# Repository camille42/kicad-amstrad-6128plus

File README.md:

# kicad-amstrad-6128plus

My first big project with Kicad.

As i'm not an expert, don't expect everything to be perfect in the first release.

For the first release, i focussed on :
    ** Memory
    ** RGB signal

* For Schematics :
    There is differences between the hardware & schematics & documentation
    ** Some values for resistors are different
    ** the R182 is replaced by a bridge & not present in the documentation
    ** ...

* For PCB :
    I can't find proper elements like keyboard connector, RJ6, centronic, so as it takes
    time to produce, it is not yet correct.

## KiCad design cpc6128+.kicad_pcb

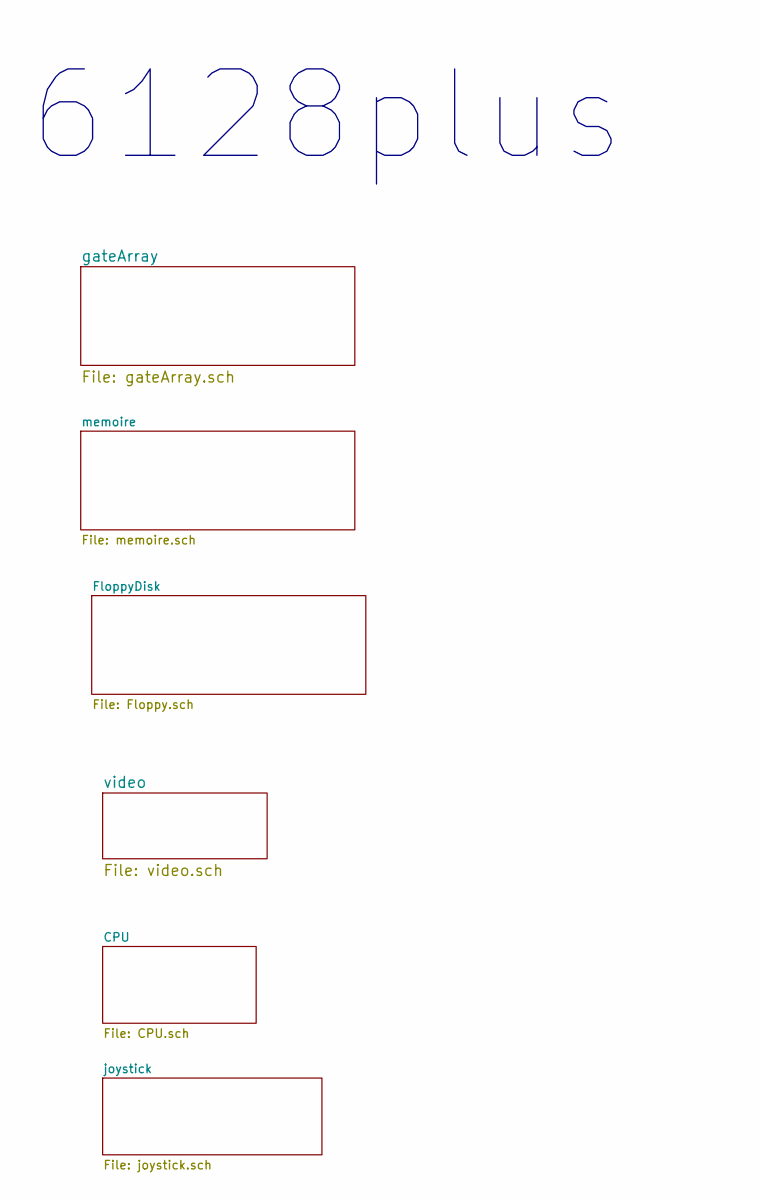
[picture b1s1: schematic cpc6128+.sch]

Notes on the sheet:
6128plus

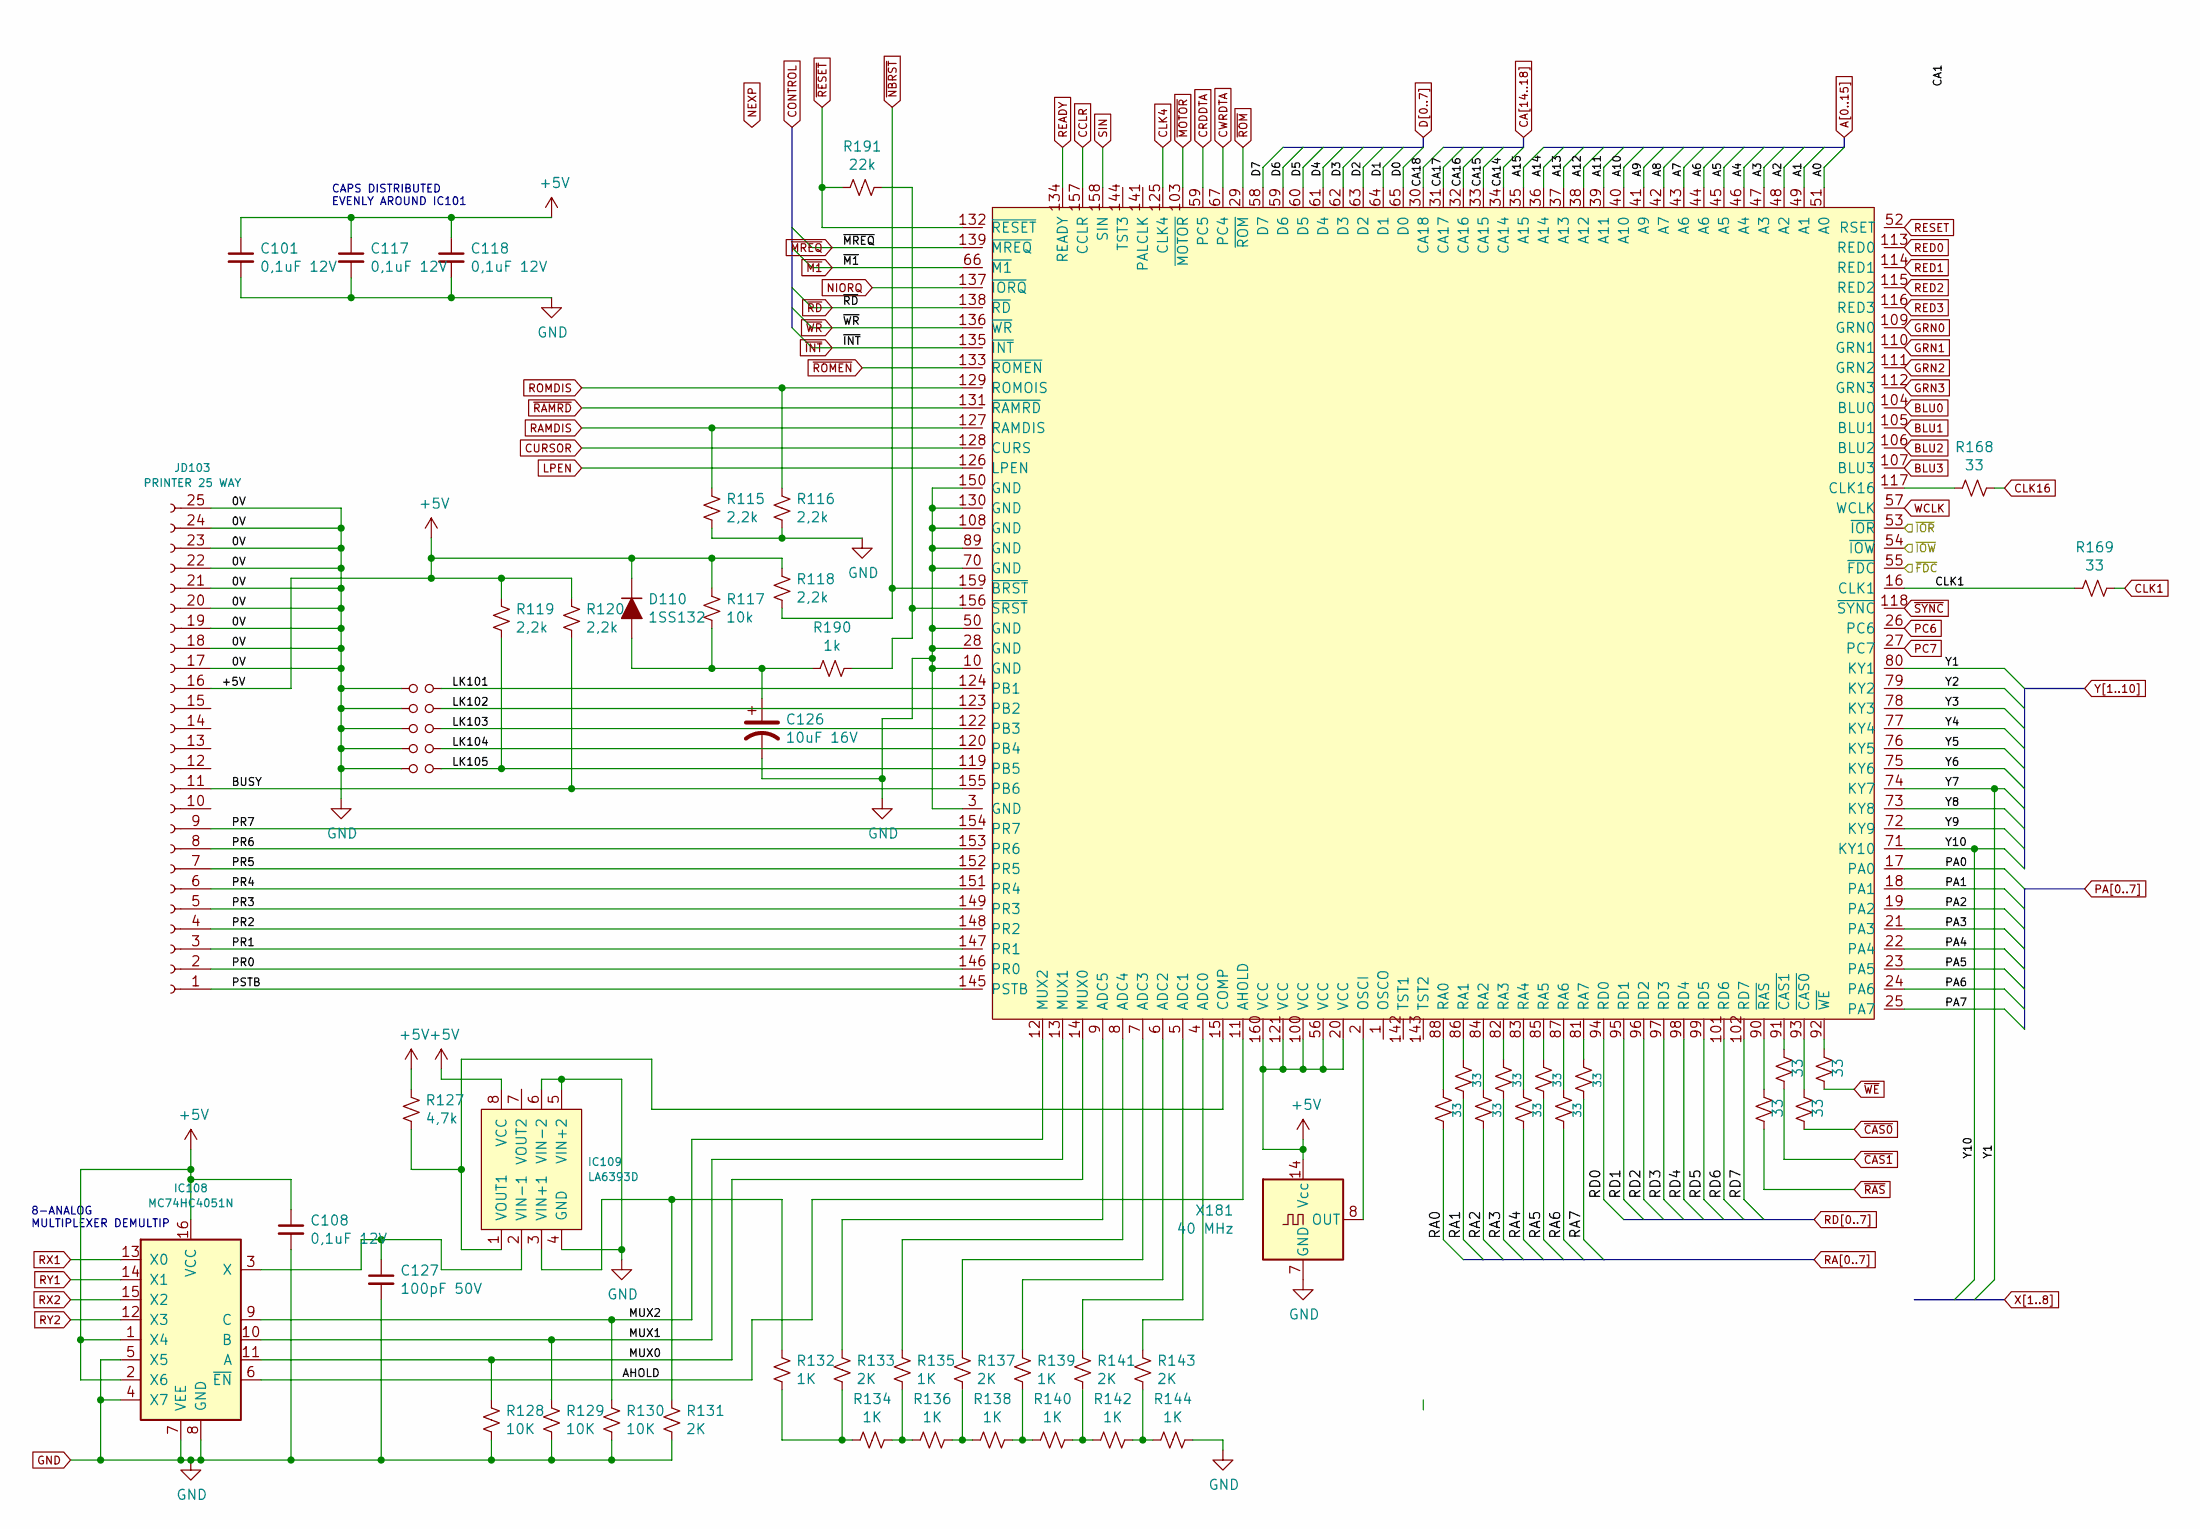
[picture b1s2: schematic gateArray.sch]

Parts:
C101, C108, C117, C118: 0,1uF 12V; C_Disc_D5.0mm_W2.5mm_P5.00mm
C126: 10uF 16V; CP_Radial_D5.0mm_P2.50mm
C127: 100pF 50V; C_Disc_D5.0mm_W2.5mm_P5.00mm
D110: 1SS132; D_A-405_P7.62mm_Horizontal
IC101: AMS40489; QFP-160_28x28_Pitch0.7mm
IC108: MC74HC4051N; DIP-16_W7.62mm
IC109: LA6393D; DIP-8_W7.62mm
JD103: PRINTER 25 WAY; DSUB-25_Male_Horizontal_P2.77x2.84mm_EdgePinOffset4.94mm_Ho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
LK101, LK102, LK103, LK104, LK105: Jumper_NO_Small
R115, R116, R118, R119, R120: 2,2k; R_Axial_DIN0204_L3.6mm_D1.6mm_P5.08mm_Horizontal
R117: 10k; R_Axial_DIN0204_L3.6mm_D1.6mm_P5.08mm_Horizontal
R127: 4,7k; R_Axial_DIN0204_L3.6mm_D1.6mm_P5.08mm_Horizontal
R128, R129, R130: 10K; R_Axial_DIN0204_L3.6mm_D1.6mm_P5.08mm_Horizontal
R131, R133, R137, R141, R143: 2K; R_Axial_DIN0204_L3.6mm_D1.6mm_P5.08mm_Horizontal
R132, R134, R135, R136, R138, R139, R140, R142, R144: 1K; R_Axial_DIN0204_L3.6mm_D1.6mm_P5.08mm_Horizontal
R146, R147, R148, R149, R150, R151, R152, R153, R154, R155, R156, R157, R168, R169: 33; R_Axial_DIN0204_L3.6mm_D1.6mm_P5.08mm_Horizontal
R190: 1k; R_Axial_DIN0204_L3.6mm_D1.6mm_P5.08mm_Horizontal
R191: 22k; R_Axial_DIN0204_L3.6mm_D1.6mm_P5.08mm_Horizontal
X181: 40 MHz; Oscillator_X181_DIP-14

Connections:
/FloppyDisk/~FDC: IC101.55 (~FDC); also elsewhere on the board
/FloppyDisk/~IOR: IC101.53 (~IOR); also elsewhere on the board
/FloppyDisk/~IOW: IC101.54 (~IOW); also elsewhere on the board
/gateArray/AHOLD: IC101.11 (AHOLD), IC108.6 (~EN)
/gateArray/BUSY: IC101.155 (PB6), JD103.11, R120.2; also elsewhere on the board
/gateArray/MUX0: IC101.14 (MUX0), IC108.11 (A), R128.1
/gateArray/MUX1: IC101.13 (MUX1), IC108.10 (B), R129.1
/gateArray/MUX2: IC101.12 (MUX2), IC108.9 (C), R130.1
/gateArray/PR0: IC101.146 (PR0), JD103.2
/gateArray/PR1: IC101.147 (PR1), JD103.3; also elsewhere on the board
/gateArray/PR2: IC101.148 (PR2), JD103.4; also elsewhere on the board
/gateArray/PR3: IC101.149 (PR3), JD103.5; also elsewhere on the board
/gateArray/PR4: IC101.151 (PR4), JD103.6; also elsewhere on the board
/gateArray/PR5: IC101.152 (PR5), JD103.7; also elsewhere on the board
/gateArray/PR6: IC101.153 (PR6), JD103.8; also elsewhere on the board
/gateArray/PR7: IC101.154 (PR7), JD103.9; also elsewhere on the board
/gateArray/PSTB: IC101.145 (PSTB), JD103.1
A0: IC101.51 (A0); also elsewhere on the board
A1: IC101.49 (A1); also elsewhere on the board
A2: IC101.48 (A2); also elsewhere on the board
A3: IC101.47 (A3); also elsewhere on the board
A4: IC101.46 (A4); also elsewhere on the board
A5: IC101.45 (A5); also elsewhere on the board
A6: IC101.44 (A6); also elsewhere on the board
A7: IC101.43 (A6); also elsewhere on the board
A8: C101.1, C108.1, C117.1, C118.1, D110.1 (K), IC101.20 (VCC), IC101.42 (A7), IC101.56 (VCC), IC101.100 (VCC), IC101.121 (VCC), IC101.160 (VCC), IC108.1 (X4), IC108.2 (X6), IC108.16 (VCC), IC109.8 (VCC), JD103.16, R117.1, R118.1, R119.1, R120.1, R127.1, X181.14 (Vcc); also elsewhere on the board
A9: IC101.41 (A9); also elsewhere on the board
A10: IC101.40 (A10); also elsewhere on the board
A11: IC101.39 (A11); also elsewhere on the board
A12: IC101.38 (A12); also elsewhere on the board
A13: IC101.37 (A13); also elsewhere on the board
A14: IC101.36 (A14); also elsewhere on the board
A15: IC101.35 (A15); also elsewhere on the board
BLU0: IC101.104 (BLU0); also elsewhere on the board
BLU1: IC101.105 (BLU1); also elsewhere on the board
BLU2: IC101.106 (BLU2); also elsewhere on the board
BLU3: IC101.107 (BLU3); also elsewhere on the board
CA14: IC101.34 (CA14); also elsewhere on the board
CA15: IC101.33 (CA15); also elsewhere on the board
CA16: IC101.32 (CA16); also elsewhere on the board
CA17: IC101.31 (CA17); also elsewhere on the board
CA18: IC101.30 (CA18); also elsewhere on the board
CCLR: IC101.157 (CCLR); also elsewhere on the board
CLK1: IC101.16 (CLK1), R169.1, R169.2; also elsewhere on the board
CLK4: IC101.125 (CLK4); also elsewhere on the board
CLK16: R168.2; also elsewhere on the board
CURSOR: IC101.128 (CURS); also elsewhere on the board
CWRDTA: IC101.67 (PC4)
D0: IC101.65 (D0); also elsewhere on the board
D1: IC101.64 (D1); also elsewhere on the board
D2: IC101.63 (D2); also elsewhere on the board
D3: IC101.62 (D3); also elsewhere on the board
D4: IC101.61 (D4); also elsewhere on the board
D5: IC101.60 (D5); also elsewhere on the board
D7: IC101.58 (D7); also elsewhere on the board
GRN0: IC101.109 (GRN0); also elsewhere on the board
GRN1: IC101.110 (GRN1); also elsewhere on the board
GRN2: IC101.111 (GRN2); also elsewhere on the board
GRN3: IC101.112 (GRN3); also elsewhere on the board
LPEN: IC101.126 (LPEN); also elsewhere on the board
NIORQ: IC101.137 (~IORQ)
unnamed: C126.1, D110.2 (A), R117.2, R190.2
unnamed: C127.1, IC108.3 (X), IC109.2 (VIN-1)
unnamed: IC101.2 (OSCI), X181.8 (OUT)
unnamed: IC101.4 (ADC0), R143.1
unnamed: IC101.5 (ADC1), R141.1
unnamed: IC101.6 (ADC2), R139.1
unnamed: IC101.7 (ADC3), R137.1
unnamed: IC101.8 (ADC4), R135.1
unnamed: IC101.9 (ADC5), R133.1
unnamed: IC101.15 (COMP), IC109.1 (VOUT1), R127.2
unnamed: IC101.81 (RA7), R153.1
unnamed: IC101.82 (RA3), R149.1
unnamed: IC101.83 (RA4), R150.1
unnamed: IC101.84 (RA2), R148.1
unnamed: IC101.85 (RA5), R151.1
unnamed: IC101.86 (RA1), R147.1
unnamed: IC101.87 (RA6), R152.1
unnamed: IC101.88 (RA0), R146.1
unnamed: IC101.90 (~RAS), R154.1
unnamed: IC101.91 (~CAS1), R155.1
unnamed: IC101.92 (~WE), R157.1
unnamed: IC101.93 (~CAS0), R156.1
unnamed: IC101.117 (CLK16), R168.1
unnamed: IC101.156 (~SRST), R190.1, R191.1
unnamed: IC109.3 (VIN+1), R131.1, R132.1
unnamed: R132.2, R133.2, R134.2
unnamed: R134.1, R135.2, R136.2
unnamed: R136.1, R137.2, R138.2
unnamed: R138.1, R139.2, R140.2
unnamed: R140.1, R141.2, R142.2
unnamed: R142.1, R143.2, R144.2
PA0: IC101.17 (PA0); also elsewhere on the board
PA1: IC101.18 (PA1); also elsewhere on the board
PA2: IC101.19 (PA2); also elsewhere on the board
PA3: IC101.21 (PA3); also elsewhere on the board
PA4: IC101.22 (PA4); also elsewhere on the board
PA5: IC101.23 (PA5); also elsewhere on the board
PA6: IC101.24 (PA6); also elsewhere on the board
PA7: IC101.25 (PA7); also elsewhere on the board
PC6: IC101.26 (PC6); also elsewhere on the board
PC7: IC101.27 (PC7); also elsewhere on the board
RA0: R146.2; also elsewhere on the board
RA1: R147.2; also elsewhere on the board
RA2: R148.2; also elsewhere on the board
RA3: R149.2; also elsewhere on the board
RA4: R150.2; also elsewhere on the board
RA5: R151.2; also elsewhere on the board
RA6: R152.2; also elsewhere on the board
RA7: R153.2; also elsewhere on the board
RAMDIS: IC101.127 (RAMDIS), R115.1; also elsewhere on the board
RD0: IC101.94 (RD0); also elsewhere on the board
RD1: IC101.95 (RD1); also elsewhere on the board
RD2: IC101.96 (RD2); also elsewhere on the board
RD3: IC101.97 (RD3); also elsewhere on the board
RD4: IC101.98 (RD4); also elsewhere on the board
RD5: IC101.99 (RD5); also elsewhere on the board
RD6: IC101.101 (RD6); also elsewhere on the board
RD7: IC101.102 (RD7); also elsewhere on the board
READY: IC101.134 (READY); also elsewhere on the board
RED0: IC101.113 (RED0); also elsewhere on the board
RED1: IC101.114 (RED1); also elsewhere on the board
RED2: IC101.115 (RED2); also elsewhere on the board
RED3: IC101.116 (RED3); also elsewhere on the board
RESET: IC101.52 (RSET); also elsewhere on the board
ROMDIS: IC101.129 (ROMOIS), R116.1; also elsewhere on the board
RX1: IC108.13 (X0); also elsewhere on the board
RX2: IC108.15 (X2); also elsewhere on the board
RY1: IC108.14 (X1); also elsewhere on the board
RY2: IC108.12 (X3); also elsewhere on the board
SIN: IC101.158 (SIN); also elsewhere on the board
WCLK: IC101.57 (WCLK); also elsewhere on the board
Y1: IC101.74 (KY7), IC101.80 (KY1); also elsewhere on the board
Y2: IC101.79 (KY2); also elsewhere on the board
Y3: IC101.78 (KY3); also elsewhere on the board
Y4: IC101.77 (KY4); also elsewhere on the board
Y5: IC101.76 (KY5); also elsewhere on the board
Y6: IC101.75 (KY6); also elsewhere on the board
Y8: IC101.73 (KY8); also elsewhere on the board
Y9: IC101.72 (KY9); also elsewhere on the board
Y10: IC101.71 (KY10); also elsewhere on the board
~CAS0: R156.2; also elsewhere on the board
~CAS1: R155.2; also elsewhere on the board
~INT: IC101.135 (~INT); also elsewhere on the board
~M1: IC101.66 (~M1); also elsewhere on the board
~MOTOR: IC101.103 (~MOTOR); also elsewhere on the board
~MREQ: IC101.139 (~MREQ); also elsewhere on the board
~NBRST: IC101.159 (~BRST), R118.2
~RAMRD: IC101.131 (~RAMRD); also elsewhere on the board
~RAS: R154.2; also elsewhere on the board
~RD: IC101.138 (~RD); also elsewhere on the board
~RESET: IC101.132 (~RESET), R191.2; also elsewhere on the board
~ROM: IC101.29 (~ROM); also elsewhere on the board
~ROMEN: IC101.133 (~ROMEN); also elsewhere on the board
~SYNC: IC101.118 (~SYNC); also elsewhere on the board
~WE: R157.2
~WR: IC101.136 (~WR); also elsewhere on the board

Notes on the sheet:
8-ANALOG MULTIPLEXER DEMULTIP
CAPS DISTRIBUTED EVENLY AROUND IC101

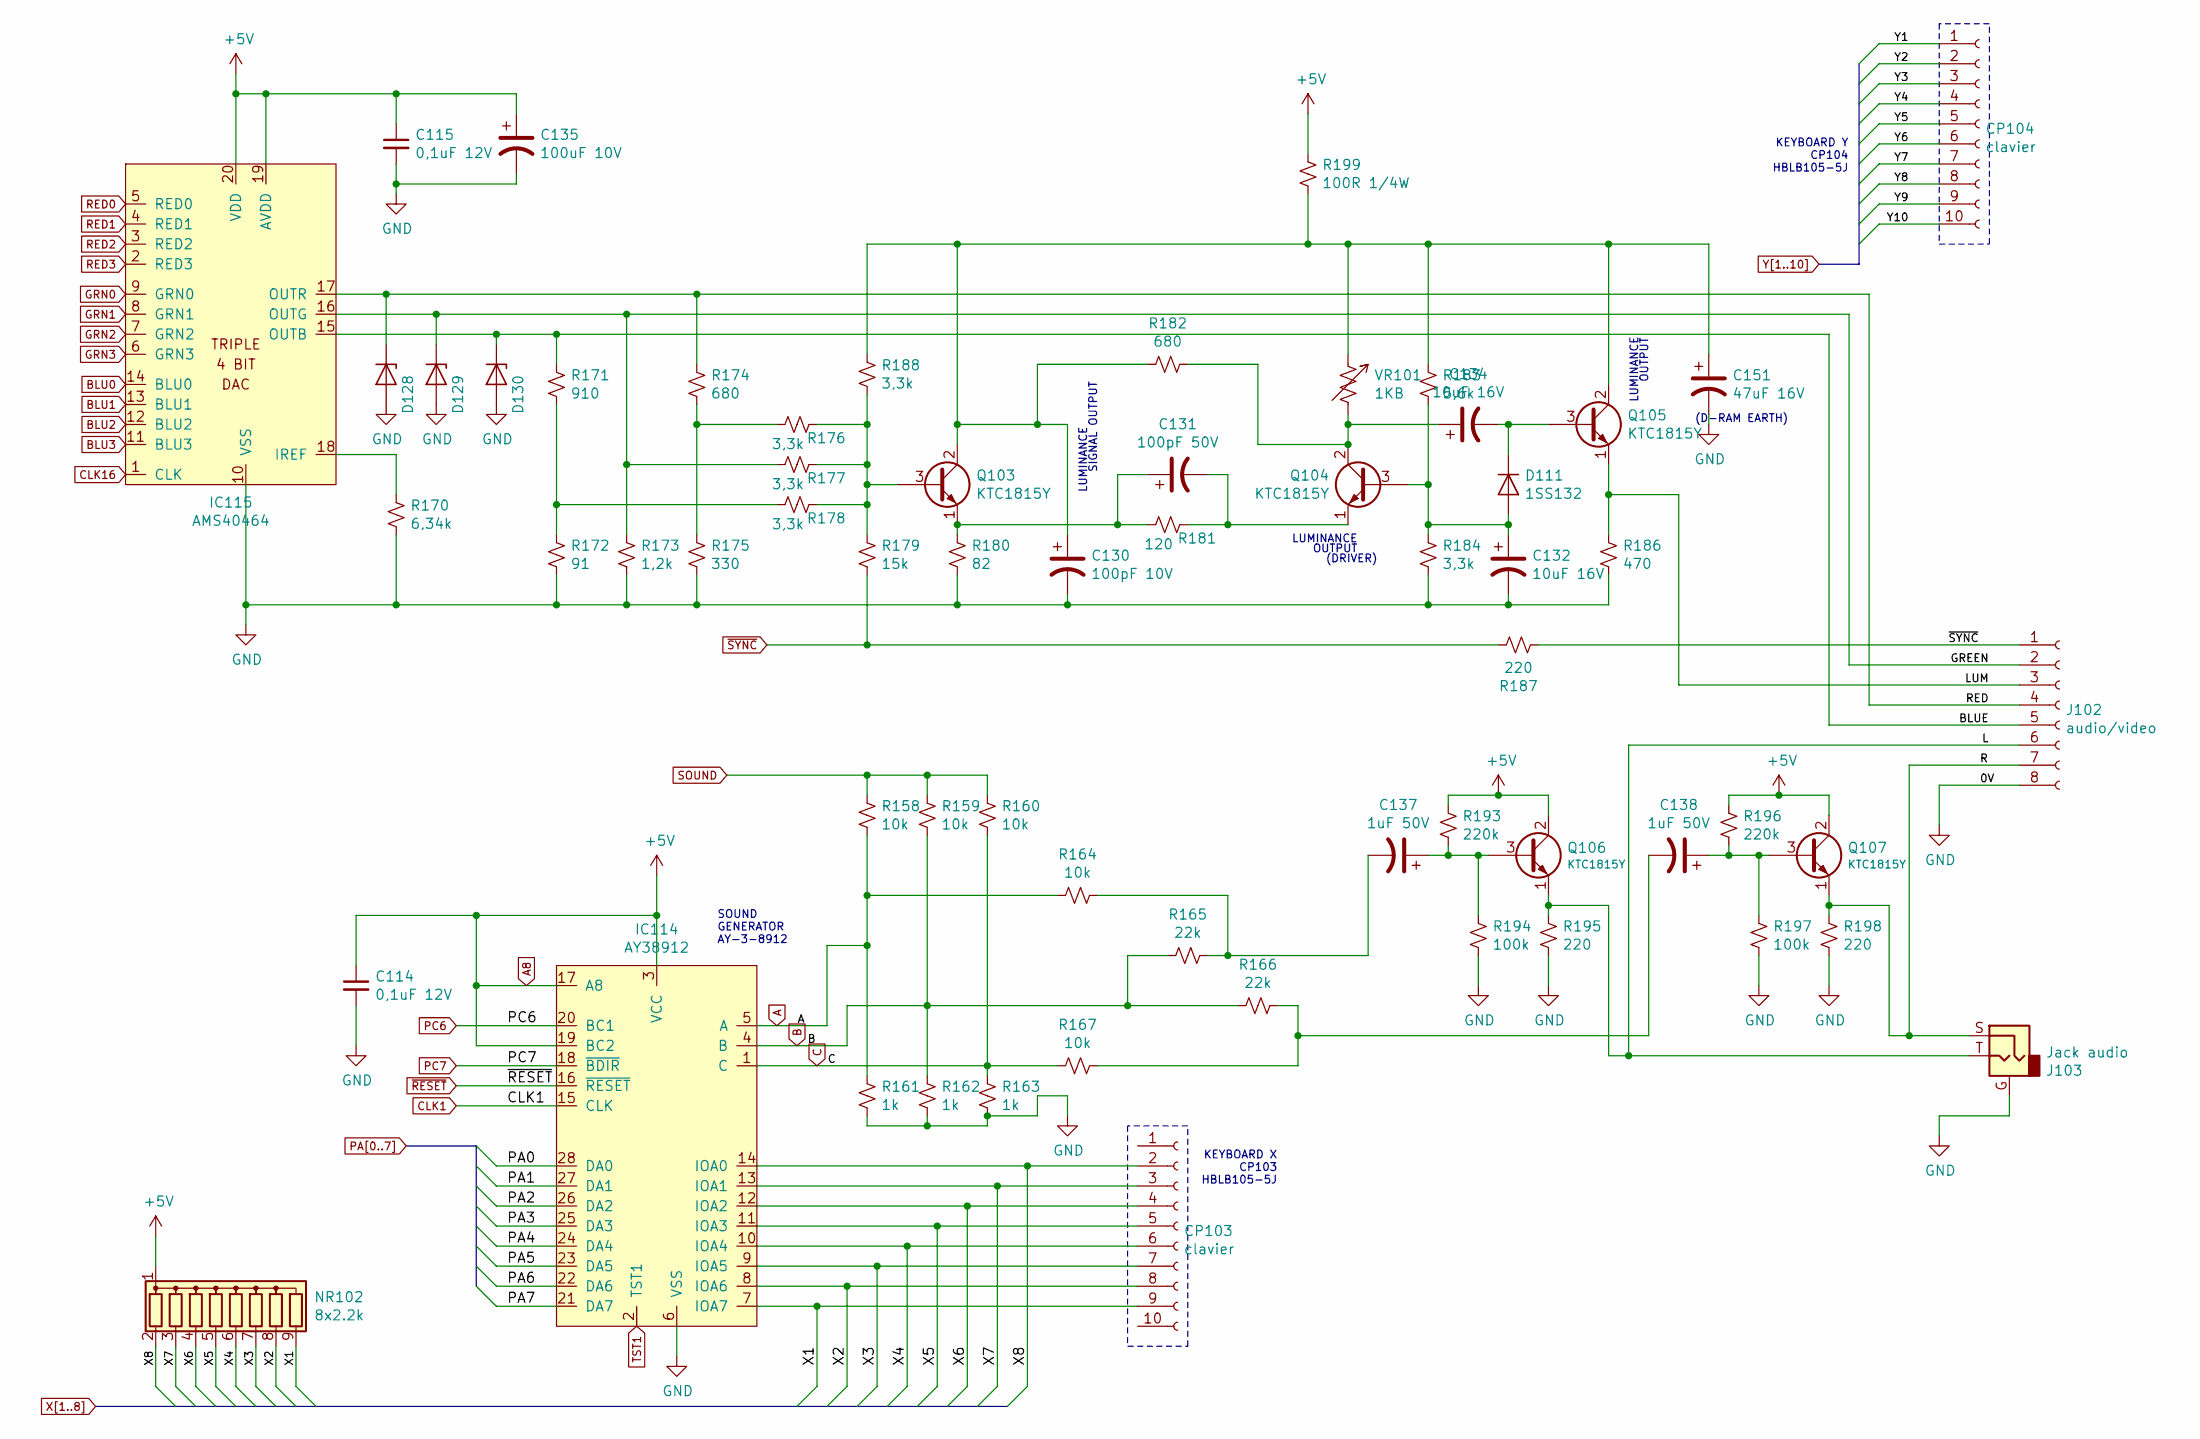
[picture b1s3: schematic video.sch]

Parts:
C114, C115: 0,1uF 12V; C_Disc_D5.0mm_W2.5mm_P5.00mm
C130: 100pF 10V; CP_Radial_D8.0mm_P5.00mm
C131: 100pF 50V; C_Disc_D5.0mm_W2.5mm_P5.00mm
C132, C134: 10uF 16V; CP_Radial_D5.0mm_P2.50mm
C135: 100uF 10V; CP_Radial_D8.0mm_P5.00mm
C137, C138: 1uF 50V; CP_Radial_D5.0mm_P2.50mm
C151: 47uF 16V; CP_Radial_D5.0mm_P2.50mm
CP103, CP104: clavier; CP_103_104
D111: 1SS132; D_DO-41_SOD81_P5.08mm_Vertical_AnodeUp
D128, D129, D130: MTZ4.7B; D_A-405_P5.08mm_Vertical_AnodeUp
IC114: AY38912; DIP-28_W15.24mm
IC115: AMS40464; DIP-20_W7.62mm
J102: audio/video; DIN8
J103: Jack audio; Jack_6128
NR102: 8x2.2k; R_Array_SIP9
Q103, Q104, Q105, Q106, Q107: KTC1815Y; TO-92_Inline_Wide
R158, R159, R160, R164, R167: 10k; R_Axial_DIN0204_L3.6mm_D1.6mm_P5.08mm_Horizontal
R161, R162, R163: 1k; R_Axial_DIN0204_L3.6mm_D1.6mm_P5.08mm_Horizontal
R165, R166: 22k; R_Axial_DIN0204_L3.6mm_D1.6mm_P5.08mm_Horizontal
R170: 6,34k; R_Axial_DIN0204_L3.6mm_D1.6mm_P5.08mm_Horizontal
R171: 910; R_Axial_DIN0204_L3.6mm_D1.6mm_P5.08mm_Horizontal
R172: 91; R_Axial_DIN0204_L3.6mm_D1.6mm_P5.08mm_Horizontal
R173: 1,2k; R_Axial_DIN0204_L3.6mm_D1.6mm_P5.08mm_Horizontal
R174, R182: 680; R_Axial_DIN0204_L3.6mm_D1.6mm_P5.08mm_Horizontal
R175: 330; R_Axial_DIN0204_L3.6mm_D1.6mm_P5.08mm_Horizontal
R176, R177, R178, R184, R188: 3,3k; R_Axial_DIN0204_L3.6mm_D1.6mm_P5.08mm_Horizontal
R179: 15k; R_Axial_DIN0204_L3.6mm_D1.6mm_P5.08mm_Horizontal
R180: 82; R_Axial_DIN0204_L3.6mm_D1.6mm_P5.08mm_Horizontal
R181: 120; R_Axial_DIN0204_L3.6mm_D1.6mm_P5.08mm_Horizontal
R183: 5,6k; R_Axial_DIN0204_L3.6mm_D1.6mm_P5.08mm_Horizontal
R186: 470; R_Axial_DIN0204_L3.6mm_D1.6mm_P5.08mm_Horizontal
R187, R195, R198: 220; R_Axial_DIN0204_L3.6mm_D1.6mm_P5.08mm_Horizontal
R193, R196: 220k; R_Axial_DIN0204_L3.6mm_D1.6mm_P5.08mm_Horizontal
R194, R197: 100k; R_Axial_DIN0204_L3.6mm_D1.6mm_P5.08mm_Horizontal
R199: 100R 1/4W; R_Axial_DIN0207_L6.3mm_D2.5mm_P10.16mm_Horizontal
VR101: 1KB; R_Axial_DIN0204_L3.6mm_D1.6mm_P5.08mm_Horizontal

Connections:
/video/BLUE: D130.1 (K), IC115.15 (OUTB), J102.5, R171.1
/video/GREEN: D129.1 (K), IC115.16 (OUTG), J102.2, R173.1, R177.2
/video/L: J102.6, J103.T, Q106.1 (E), R195.1
/video/LUM: J102.3, Q105.1 (E), R186.1
/video/R: J102.7, J103.S, Q107.1 (E), R198.1
/video/RED: D128.1 (K), IC115.17 (OUTR), J102.4, R174.1
A: IC114.5 (A), R158.2, R161.1, R164.1
A8: C114.1, C115.1, C135.1, IC114.3 (VCC), IC114.17 (A8), IC114.19 (BC2), IC115.19 (AVDD), IC115.20 (VDD), NR102.1 (common), Q106.2 (C), Q107.2 (C), R193.1, R196.1, R199.1; also elsewhere on the board
B: IC114.4 (B), R159.2, R162.1, R165.1, R166.1
BLU0: IC115.14 (BLU0); also elsewhere on the board
BLU1: IC115.13 (BLU1); also elsewhere on the board
BLU2: IC115.12 (BLU2); also elsewhere on the board
BLU3: IC115.11 (BLU3); also elsewhere on the board
C: IC114.1 (C), R160.2, R163.1, R167.1
CLK1: IC114.15 (CLK); also elsewhere on the board
CLK16: IC115.1 (CLK); also elsewhere on the board
GRN0: IC115.9 (GRN0); also elsewhere on the board
GRN1: IC115.8 (GRN1); also elsewhere on the board
GRN2: IC115.7 (GRN2); also elsewhere on the board
GRN3: IC115.6 (GRN3); also elsewhere on the board
unnamed: C130.1, C151.1, Q103.2 (C), Q105.2 (C), R182.2, R183.1, R188.1, R199.2, VR101.1
unnamed: C131.1, Q103.1 (E), R180.1, R181.2
unnamed: C131.2, Q104.1 (E), R181.1
unnamed: C132.1, D111.2 (A), Q104.3 (B), R183.2, R184.1
unnamed: C134.1, Q104.2 (C), R182.1, VR101.2
unnamed: C134.2, D111.1 (K), Q105.3 (B)
unnamed: C137.1, Q106.3 (B), R193.2, R194.1
unnamed: C137.2, R164.2, R165.2
unnamed: C138.1, Q107.3 (B), R196.2, R197.1
unnamed: C138.2, R166.2, R167.2
unnamed: IC115.18 (IREF), R170.1
unnamed: Q103.3 (B), R176.1, R177.1, R178.1, R179.1, R188.2
unnamed: R171.2, R172.1, R178.2
unnamed: R174.2, R175.1, R176.2
PA0: IC114.28 (DA0); also elsewhere on the board
PA1: IC114.27 (DA1); also elsewhere on the board
PA2: IC114.26 (DA2); also elsewhere on the board
PA3: IC114.25 (DA3); also elsewhere on the board
PA4: IC114.24 (DA4); also elsewhere on the board
PA5: IC114.23 (DA5); also elsewhere on the board
PA6: IC114.22 (DA6); also elsewhere on the board
PA7: IC114.21 (DA7); also elsewhere on the board
PC6: IC114.20 (BC1); also elsewhere on the board
PC7: IC114.18 (~BDIR); also elsewhere on the board
RED0: IC115.5 (RED0); also elsewhere on the board
RED1: IC115.4 (RED1); also elsewhere on the board
RED2: IC115.3 (RED2); also elsewhere on the board
RED3: IC115.2 (RED3); also elsewhere on the board
SOUND: R158.1, R159.1, R160.1; also elsewhere on the board
TST1: IC114.2 (TST1)
X1: CP103.9, IC114.7 (IOA7), NR102.9 (R8)
X2: CP103.8, IC114.8 (IOA6), NR102.8 (R7)
X3: CP103.7, IC114.9 (IOA5), NR102.7 (R6); also elsewhere on the board
X4: CP103.6, IC114.10 (IOA4), NR102.6 (R5); also elsewhere on the board
X5: CP103.5, IC114.11 (IOA3), NR102.5 (R4); also elsewhere on the board
X6: CP103.4, IC114.12 (IOA2), NR102.4 (R3); also elsewhere on the board
X7: CP103.3, IC114.13 (IOA1), NR102.3 (R2)
X8: CP103.2, IC114.14 (IOA0), NR102.2 (R1); also elsewhere on the board
Y1: CP104.1, CP104.7; also elsewhere on the board
Y2: CP104.2; also elsewhere on the board
Y3: CP104.3; also elsewhere on the board
Y4: CP104.4; also elsewhere on the board
Y5: CP104.5; also elsewhere on the board
Y6: CP104.6; also elsewhere on the board
Y8: CP104.8; also elsewhere on the board
Y9: CP104.9; also elsewhere on the board
Y10: CP104.10; also elsewhere on the board
~RESET: IC114.16 (~RESET); also elsewhere on the board
~SYNC: J102.1, R179.2, R187.1, R187.2; also elsewhere on the board

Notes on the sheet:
LUMINANCE
SIGNAL OUTPUT
(DRIVER)
OUTPUT
(D-RAM EARTH)
KEYBOARD Y CP104 HBLB105-5J
KEYBOARD X CP103 HBLB105-5J
SOUND GENERATOR AY-3-8912

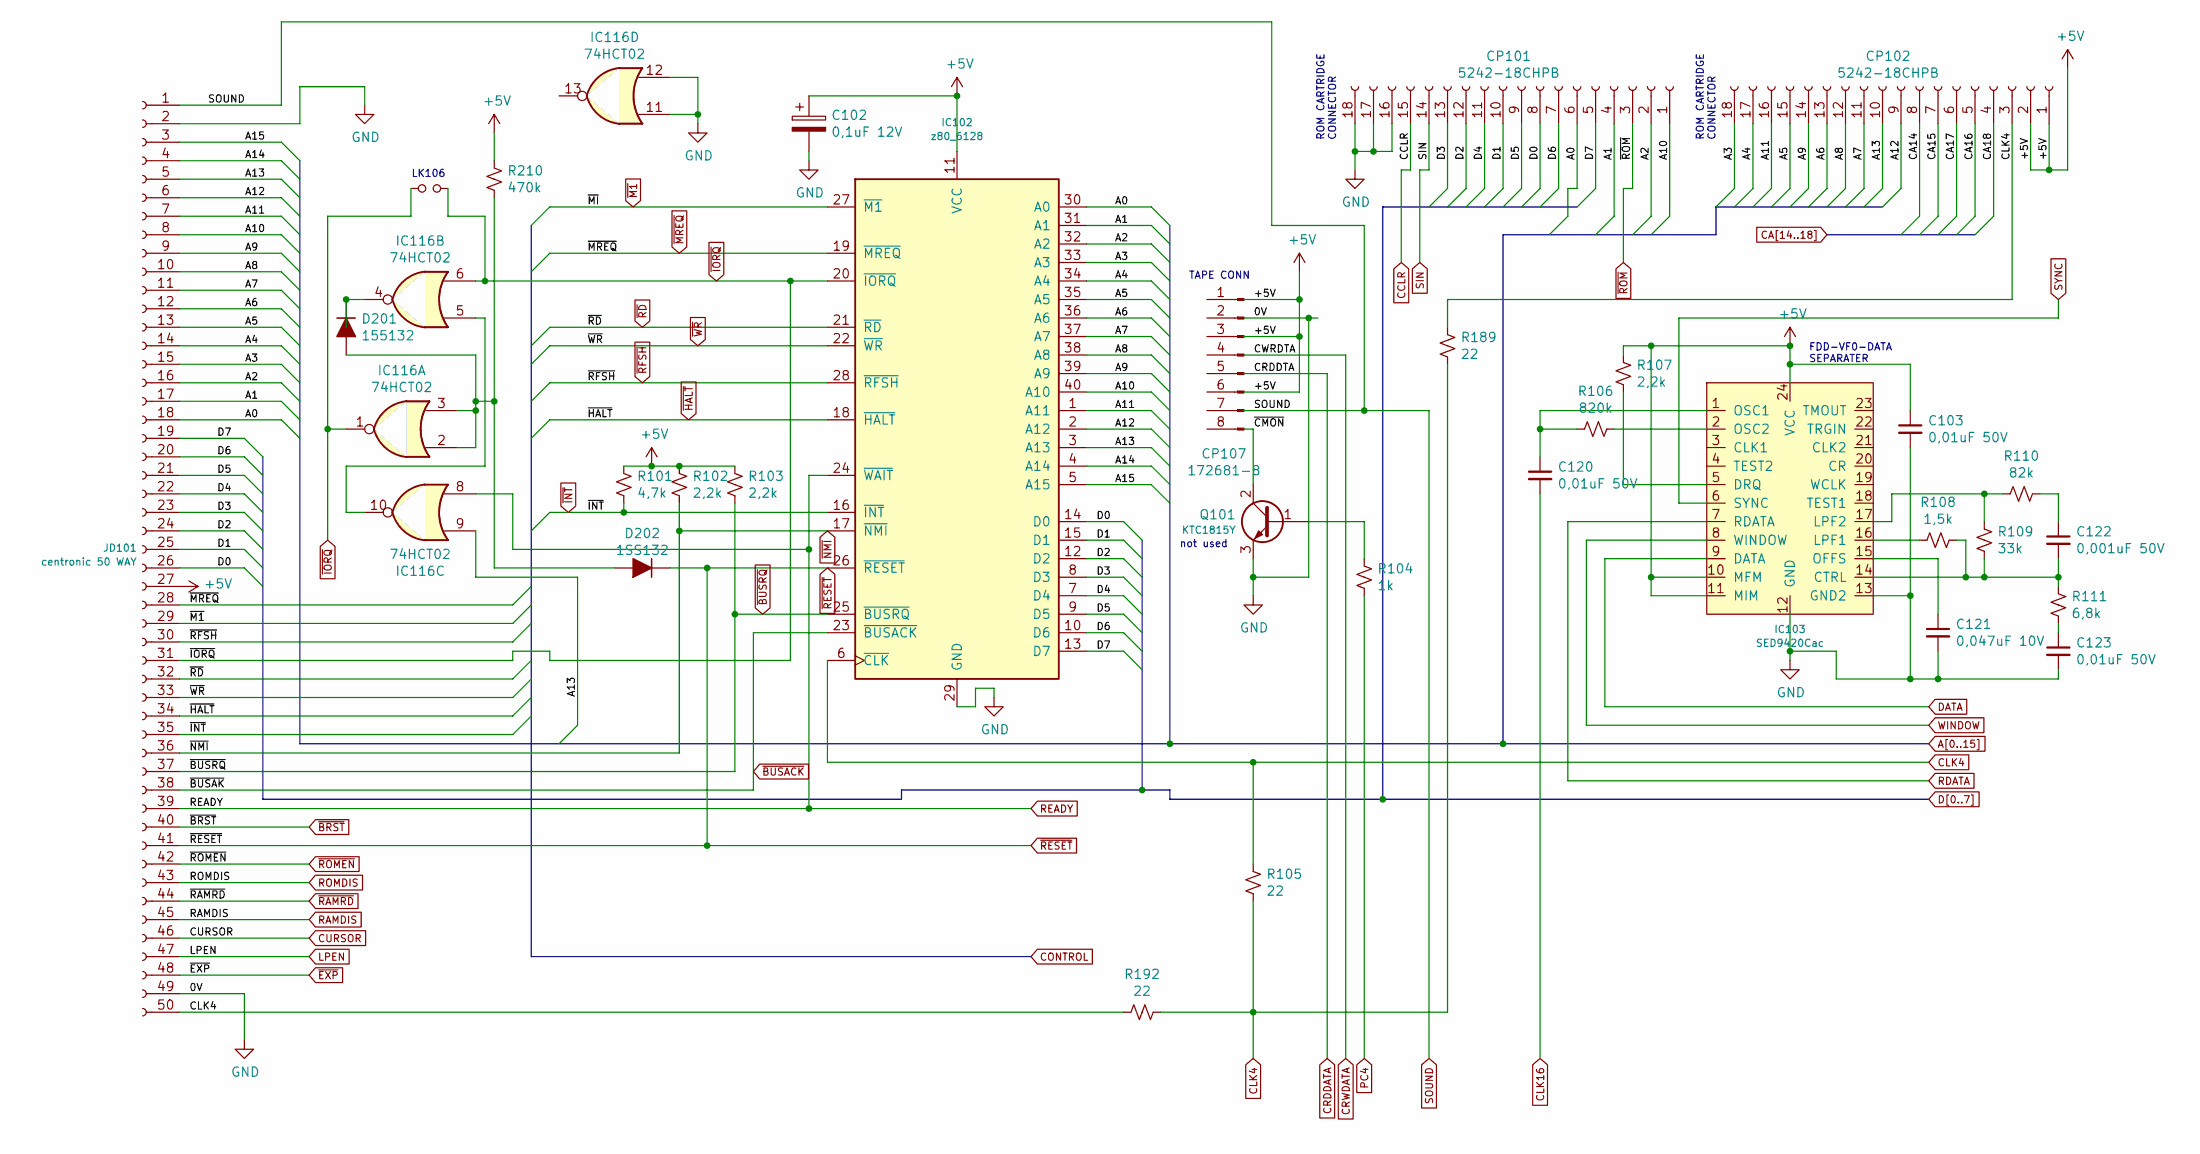
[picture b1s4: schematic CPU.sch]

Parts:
C102: 0,1uF 12V; C_Disc_D5.0mm_W2.5mm_P5.00mm
C103, C120, C123: 0,01uF 50V; C_Disc_D5.0mm_W2.5mm_P5.00mm
C121: 0,047uF 10V; C_Disc_D5.0mm_W2.5mm_P5.00mm
C122: 0,001uF 50V; C_Disc_D5.0mm_W2.5mm_P5.00mm
CP101, CP102: 5242-18CHPB; CP01_02
CP107: 172681-8; CP_107
D201: 155132; D_A-405_P5.08mm_Vertical_AnodeUp
D202: 1SS132; D_DO-41_SOD81_P5.08mm_Vertical_AnodeUp
IC102: z80_6128; DIP-40_W15.24mm
IC103: SED9420Cac; DIP-24_W15.24mm
IC116: 74HCT02; DIP-14_W7.62mm
JD101: centronic 50 WAY; centronic_50
LK106: Jumper_NO_Small
Q101: KTC1815Y; TO-92_Inline_Wide
R101: 4,7k; R_Axial_DIN0204_L3.6mm_D1.6mm_P5.08mm_Horizontal
R102, R103, R107: 2,2k; R_Axial_DIN0204_L3.6mm_D1.6mm_P5.08mm_Horizontal
R104: 1k; R_Axial_DIN0204_L3.6mm_D1.6mm_P5.08mm_Horizontal
R105, R189, R192: 22; R_Axial_DIN0204_L3.6mm_D1.6mm_P5.08mm_Horizontal
R106: 820k; R_Axial_DIN0204_L3.6mm_D1.6mm_P5.08mm_Horizontal
R108: 1,5k; R_Axial_DIN0204_L3.6mm_D1.6mm_P5.08mm_Horizontal
R109: 33k; R_Axial_DIN0204_L3.6mm_D1.6mm_P5.08mm_Horizontal
R110: 82k; R_Axial_DIN0204_L3.6mm_D1.6mm_P5.08mm_Horizontal
R111: 6,8k; R_Axial_DIN0204_L3.6mm_D1.6mm_P5.08mm_Horizontal
R210: 470k; R_Axial_DIN0207_L6.3mm_D2.5mm_P10.16mm_Horizontal

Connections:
/CPU/~CMON: Q101.2 (C)
A0: CP101.6, IC102.30 (A0), JD101.18; also elsewhere on the board
A1: CP101.4, IC102.31 (A1), JD101.17; also elsewhere on the board
A2: CP101.2, IC102.32 (A2), JD101.16; also elsewhere on the board
A3: CP102.18, IC102.33 (A3), JD101.15; also elsewhere on the board
A4: CP102.17, IC102.34 (A4), JD101.14; also elsewhere on the board
A5: CP102.15, IC102.35 (A5), JD101.13; also elsewhere on the board
A6: CP102.13, IC102.36 (A6), JD101.12; also elsewhere on the board
A7: CP102.11, IC102.37 (A7), JD101.11; also elsewhere on the board
A8: C102.1, C103.1, CP102.1, CP102.2, CP102.12, IC102.11 (VCC), IC102.38 (A8), IC103.10 (MFM), IC103.11 (MIM), IC103.24 (VCC), JD101.10, JD101.27, R101.1, R102.1, R103.1, R107.1, R210.1; also elsewhere on the board
A9: CP102.14, IC102.39 (A9), JD101.9; also elsewhere on the board
A10: CP101.1, IC102.40 (A10), JD101.8; also elsewhere on the board
A11: CP102.16, IC102.1 (A11), JD101.7; also elsewhere on the board
A12: CP102.9, IC102.2 (A12), JD101.6; also elsewhere on the board
A13: CP102.10, IC102.3 (A13), IC116.9, JD101.5; also elsewhere on the board
A14: IC102.4 (A14), JD101.4; also elsewhere on the board
A15: IC102.5 (A15), JD101.3; also elsewhere on the board
CA14: CP102.8; also elsewhere on the board
CA15: CP102.7; also elsewhere on the board
CA16: CP102.5; also elsewhere on the board
CA17: CP102.6; also elsewhere on the board
CA18: CP102.4; also elsewhere on the board
CCLR: CP101.15; also elsewhere on the board
CLK4: CP102.3, IC102.6 (~CLK~), JD101.50, R105.1, R105.2, R189.1, R189.2, R192.1, R192.2; also elsewhere on the board
CLK16: C120.2; also elsewhere on the board
CURSOR: JD101.46; also elsewhere on the board
D0: CP101.8, IC102.14 (D0), JD101.26; also elsewhere on the board
D1: CP101.10, IC102.15 (D1), JD101.25; also elsewhere on the board
D2: CP101.12, IC102.12 (D2), JD101.24; also elsewhere on the board
D3: CP101.13, IC102.8 (D3), JD101.23; also elsewhere on the board
D4: CP101.11, IC102.7 (D4), JD101.22; also elsewhere on the board
D5: CP101.9, IC102.9 (D5), JD101.21; also elsewhere on the board
D6: CP101.7, IC102.10 (D6), JD101.20; also elsewhere on the board
D7: CP101.5, IC102.13 (D7), JD101.19; also elsewhere on the board
DATA: IC103.9 (DATA); also elsewhere on the board
LPEN: JD101.47; also elsewhere on the board
unnamed: C120.1, IC103.1 (OSC1), R106.1
unnamed: C121.1, IC103.15 (OFFS)
unnamed: C122.1, R110.2
unnamed: C122.2, IC103.14 (CTRL), R108.2, R109.2, R111.1
unnamed: C123.1, R111.2
unnamed: D201.1 (K), IC116.4
unnamed: D201.2 (A), D202.2 (A), IC116.2, IC116.3, R210.2
unnamed: IC103.2 (OSC2), R106.2
unnamed: IC103.5 (DRQ), R107.2
unnamed: IC103.16 (LPF1), R108.1
unnamed: IC103.17 (LPF2), R109.1, R110.1
unnamed: IC116.5, IC116.10
unnamed: Q101.1 (B), R104.1
PC4: R104.2
RAMDIS: JD101.45; also elsewhere on the board
RDATA: IC103.7 (RDATA); also elsewhere on the board
READY: IC102.24 (~WAIT~), IC116.8, JD101.39; also elsewhere on the board
ROMDIS: JD101.43; also elsewhere on the board
SIN: CP101.14; also elsewhere on the board
SOUND: JD101.1; also elsewhere on the board
SYNC: IC103.6 (SYNC); also elsewhere on the board
WINDOW: IC103.8 (WINDOW); also elsewhere on the board
~BRST: JD101.40
~BUSACK: IC102.23 (~BUSACK~), JD101.38
~BUSRQ: IC102.25 (~BUSRQ~), JD101.37, R103.2
~EXP: JD101.48
~HALT: IC102.18 (~HALT~), JD101.34
~INT: IC102.16 (~INT~), JD101.35, R101.2; also elsewhere on the board
~IORQ: IC102.20 (~IORQ~), IC116.1, IC116.6, JD101.31, LK106.1, LK106.2
~M1: IC102.27 (~M1~), JD101.29; also elsewhere on the board
~MREQ: IC102.19 (~MREQ~), JD101.28; also elsewhere on the board
~NMI: IC102.17 (~NMI~), JD101.36, R102.2
~RAMRD: JD101.44; also elsewhere on the board
~RD: IC102.21 (~RD~), JD101.32; also elsewhere on the board
~RESET: D202.1 (K), IC102.26 (~RESET~), JD101.41; also elsewhere on the board
~RFSH: IC102.28 (~RFSH~), JD101.30
~ROM: CP101.3; also elsewhere on the board
~ROMEN: JD101.42; also elsewhere on the board
~WR: IC102.22 (~WR~), JD101.33; also elsewhere on the board

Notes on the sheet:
ROM CARTRIDGE CONNECTOR
TAPE CONN
FDD-VF0-DATA SEPARATER
not used
LK106
